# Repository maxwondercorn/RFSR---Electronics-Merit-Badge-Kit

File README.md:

Electronics Merit Badge Kit
==================================

Small ATtiny (Arduino IDE Compatible) microcontroller based kit used to teach Electronics Merit Badge at Resica Falls Scout Reservation.  Once assembled and functional, the kit allows selection of various LED display modes (Flickering Candle, Nightlight, Flashlight, Etc.) by rotating the on-board potentiometer.  Kit design is intended to meet all relevant badge requirements and expose scouts to a variety of component types at the lowest cost possible.

Repository Contents
-------------------

* **/Hardware** - Eagle Schematic / PCB Layouts & Bill Of Materials
    - PCB silkscreen periodically updated to match summer camp staff members currently teaching Electronics Merit Badge at Resica Falls Scout Reservation.
    - Bill Of Materials includes vendors / part numbers from the last production run.
* **/Software** - Demo Arduino sketch for the kit.  Code is intended to be easy to understand for beginners.
* **/Images** - Images of the kit, both assembled and in parts.

Firmware Programming
-------------------

As of the 2017 summer camp season, kit firmware is programmed using the following tools:

#### Hardware
An [Arduino Uno](https://store.arduino.cc/usa/arduino-uno-rev3) and an [AVR Programmer Shield](http://www.electrodragon.com/w/AVR_Programmer_Arduino_Shield) with ZIF socket.

Image of programming rig: [/Images/ElectronicsMBProgrammingRig.jpg](https://raw.githubusercontent.com/crossfireprod/RFSR---Electronics-Merit-Badge-Kit/master/Images/ElectronicsMBProgrammingRig.jpg)

#### Software
The Arduino Uno is used as an in system programmer (ISP) through use of the [ArduinoISP](https://github.com/arduino/ArduinoISP) sketch packaged with [Arduino 1.8.3](https://www.arduino.cc/en/main/software) to program the ATtiny 45/85 targets.  ATtiny core files available from [David Mellis' GitHub Repository](https://github.com/damellis/attiny), using [full instructions published by high-low tech](http://highlowtech.org/?p=1695) allow the ATtiny AVR microcontrollers used in the kits to be programmed directly from the Arduino IDE.

License
-------------------

All contents of this repository are released under [Creative Commons Share-alike 4.0](http://creativecommons.org/licenses/by-sa/4.0/).

Kit Design By: [*ZachCross.com*](https://ZachCross.com)

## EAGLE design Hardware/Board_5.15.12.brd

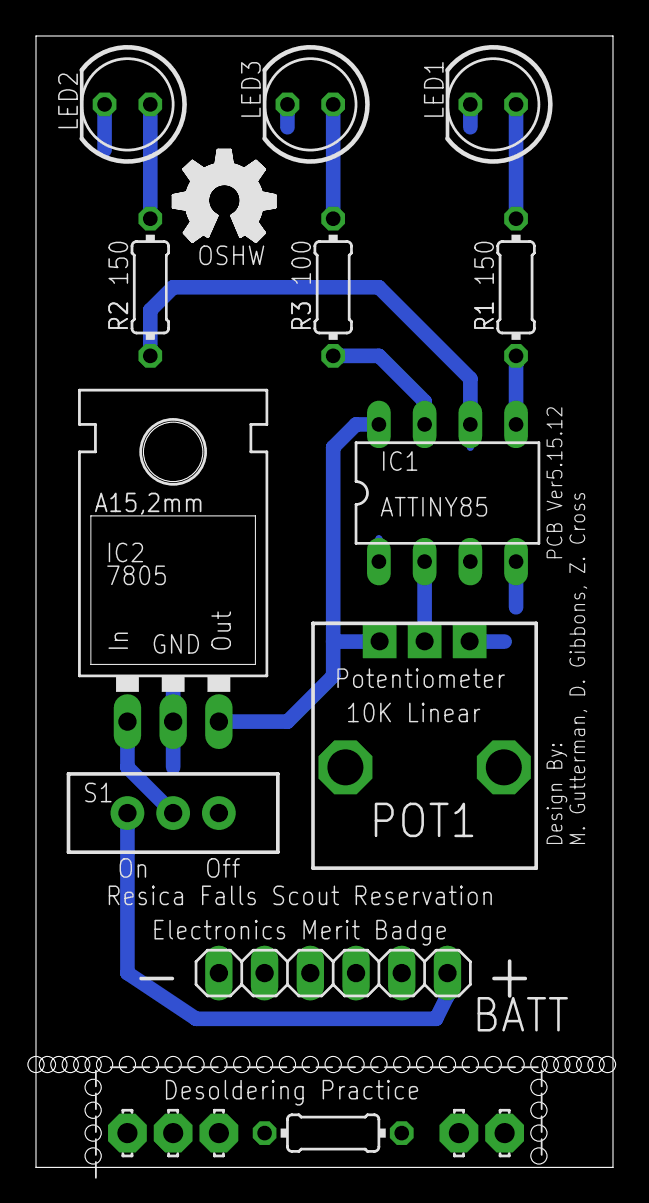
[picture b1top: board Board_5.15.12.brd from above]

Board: 2 copper layers, 32.1 x 62.9 mm, 19 parts (0 on the bottom side), 10 nets.

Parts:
10K_LIN_POT: 10K Lin Pot; ALPS_POT
7805: 78XXL
E$1, E$3: OSHW_FILLX200_NOTEXT
E$2: 1X06
E$5, E$6, E$7, E$8, E$9: LSP11
IC1: ATTiny85; DIL08
L1, L2: Yel; LED5MM
L3: Wht; LED5MM
PRACTICE: 0204/7
R1, R2, R3: 0204/7
S1: SWITCH-SPDT

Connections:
GND: 7805.GND, E$2.1, IC1.4, L1.K, L2.K, L3.K
unnamed: 7805.IN, S1.2
unnamed: L1.A, R1.2
unnamed: L2.A, R2.2
unnamed: L3.A, R3.2
S$3: IC1.5, R1.1
S$4: 7805.OUT, IC1.8
S$5: E$2.6, S1.3
S$7: IC1.6, R2.1
S$8: IC1.7, R3.1

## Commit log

2015-07-29 Electronics_MB_7_14_14.pde
    Updated the code by adding a test sequence at start up.
2017-02-03 Added supporting documentation.
2017-07-08 Added image of example programming rig.
2017-07-08 Added firmware programming information to README
2017-07-08 Fixed markdown typos.
2017-07-08 Fixed link syntax typo.
2017-07-08 Style changes
2017-07-08 Changed link display syntax.
2021-11-23 feat: Converted to KiCad
2021-11-23 chore: Eagle project imported
    Rnamed so it could be imported into KiCad
2021-11-23 Create gerber file
2021-11-23 Added missing keepout zone
